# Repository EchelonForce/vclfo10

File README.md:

# Eurorack LFO VCLFO10 

This is a PCB for a eurorack LFO based on the VCLFO10 chip from Electric Druid.

Full writeup here: https://www.robotdialogs.com/2022/09/eurorack-lfo-module-vclfo10.html

This work is licensed under a Creative Commons Attribution-NonCommercial-ShareAlike 4.0 International License. https://creativecommons.org/licenses/by-nc-sa/4.0/

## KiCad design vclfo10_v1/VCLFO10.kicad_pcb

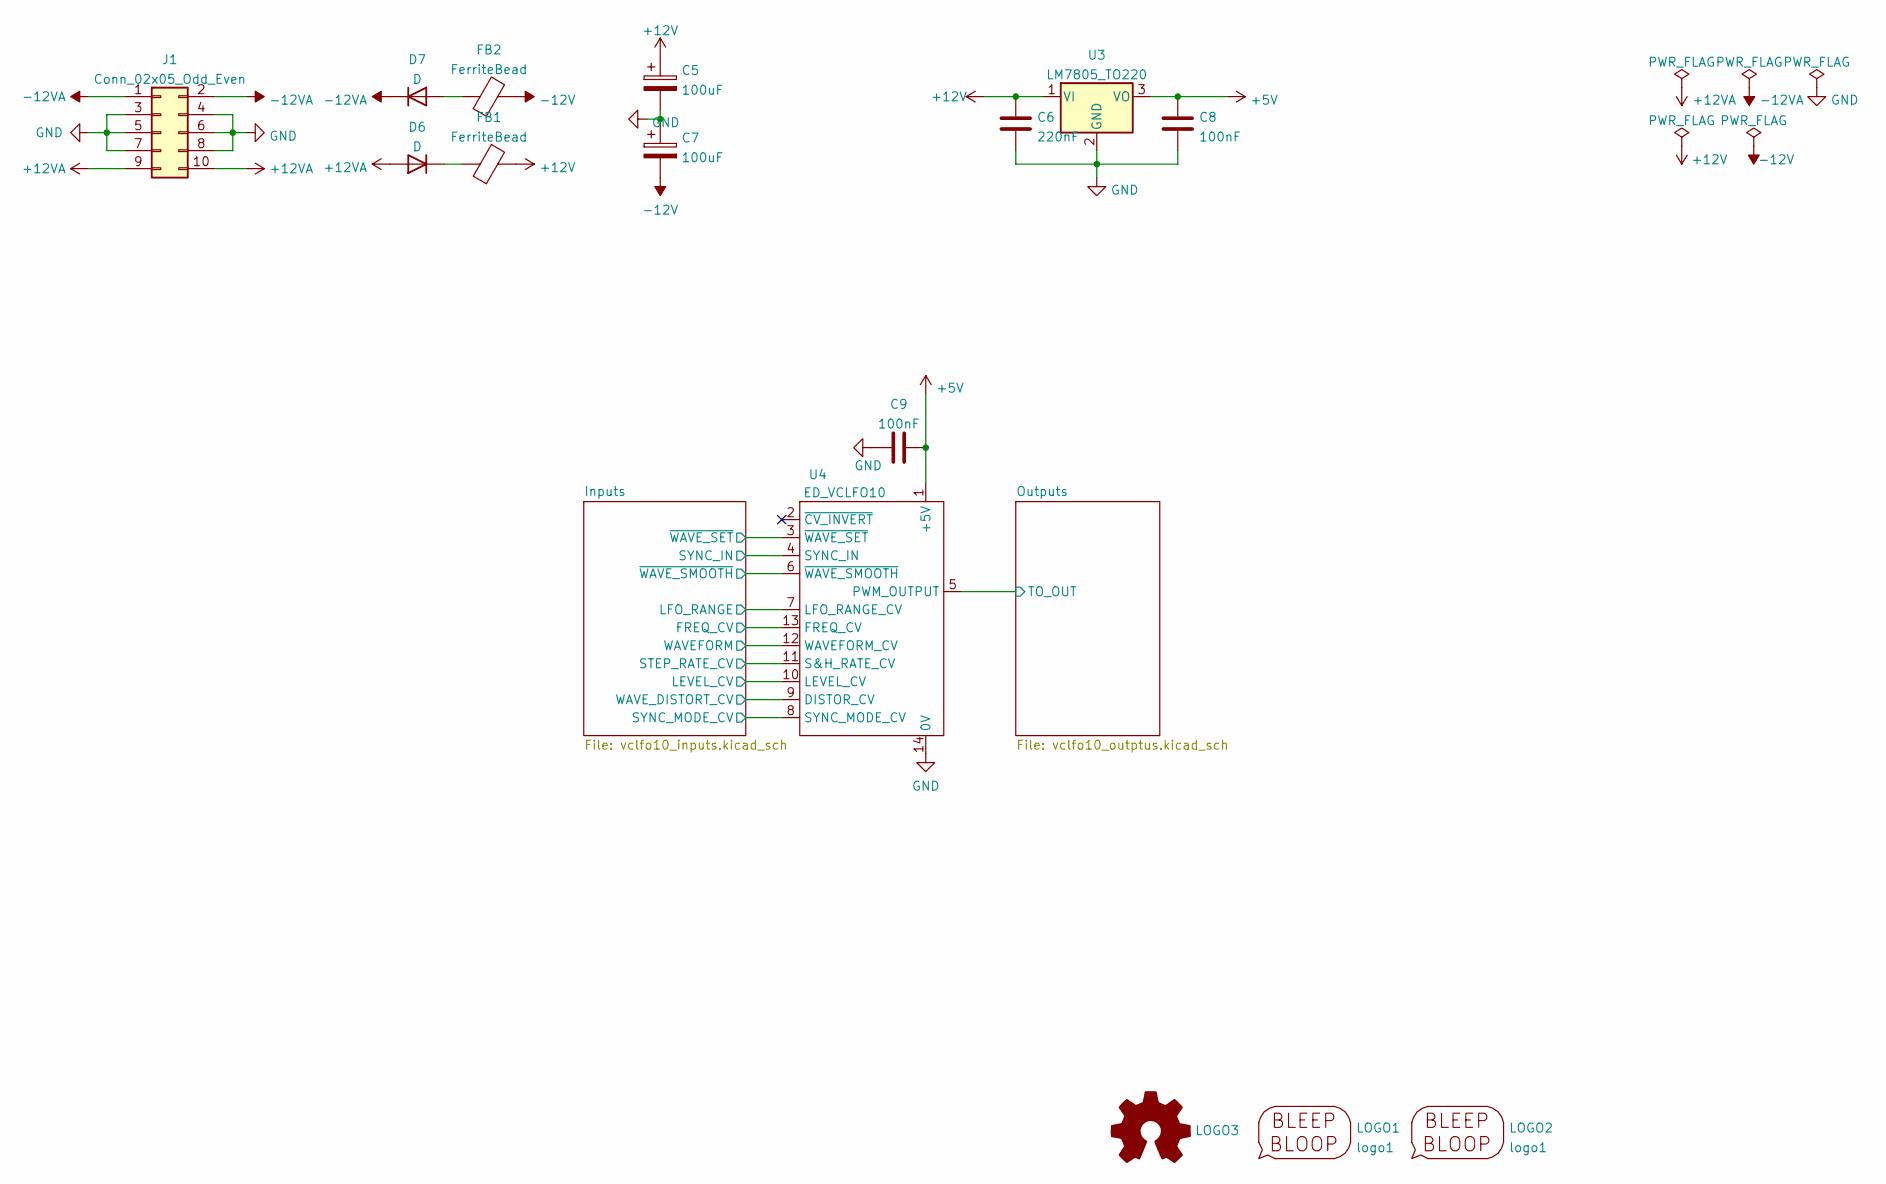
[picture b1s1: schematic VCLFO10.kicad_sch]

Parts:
C5, C7: 100uF; CP_Radial_D5.0mm_P2.50mm
C6: 220nF; C_1206_3216Metric_Pad1.33x1.80mm_HandSolder
C8, C9: 100nF; C_1206_3216Metric_Pad1.33x1.80mm_HandSolder
D6, D7: D; D_A-405_P7.62mm_Horizontal
FB1, FB2: FerriteBead; L_Axial_L6.6mm_D2.7mm_P2.54mm_Vertical_Vishay_IM-2
J1: Conn_02x05_Odd_Even; IDC-Header_2x05_P2.54mm_Vertical
LOGO1: logo1; Logo1
LOGO2: logo1; Logo2
LOGO3: Logo_Open_Hardware_Small; OSHW-Symbol_6.7x6mm_SilkScreen
U3: LM7805_TO220; TO-220-3_Vertical
U4: ED_VCLFO10; DIP-14_W7.62mm_Socket_LongPads

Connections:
+5V: C8.1, C9.2, U3.3 (VO), U4.1 (+5V); also elsewhere on the board
+12V: C5.1, C6.1, FB1.2, U3.1 (VI); also elsewhere on the board
+12VA: D6.2 (A), J1.9, J1.10
-12V: C7.2, FB2.2; also elsewhere on the board
-12VA: D7.1 (K), J1.1, J1.2
/Inputs/FREQ_CV: U4.13 (FREQ_CV); also elsewhere on the board
/Inputs/LEVEL_CV: U4.10 (LEVEL_CV); also elsewhere on the board
/Inputs/LFO_RANGE: U4.7 (LFO_RANGE_CV); also elsewhere on the board
/Inputs/STEP_RATE_CV: U4.11 (S&H_RATE_CV); also elsewhere on the board
/Inputs/SYNC_IN: U4.4 (SYNC_IN); also elsewhere on the board
/Inputs/SYNC_MODE_CV: U4.8 (SYNC_MODE_CV); also elsewhere on the board
/Inputs/WAVEFORM: U4.12 (WAVEFORM_CV); also elsewhere on the board
/Inputs/WAVE_DISTORT_CV: U4.9 (DISTOR_CV); also elsewhere on the board
/Inputs/~WAVE_SET: U4.3 (~WAVE_SET); also elsewhere on the board
/Inputs/~WAVE_SMOOTH: U4.6 (~WAVE_SMOOTH); also elsewhere on the board
/Outputs/TO_OUT: U4.5 (PWM_OUTPUT); also elsewhere on the board
GND: C5.2, C6.2, C7.1, C8.2, C9.1, J1.3, J1.4, J1.5, J1.6, J1.7, J1.8, U3.2 (GND), U4.14 (0V); also elsewhere on the board
unnamed: D6.1 (K), FB1.1
unnamed: D7.2 (A), FB2.1

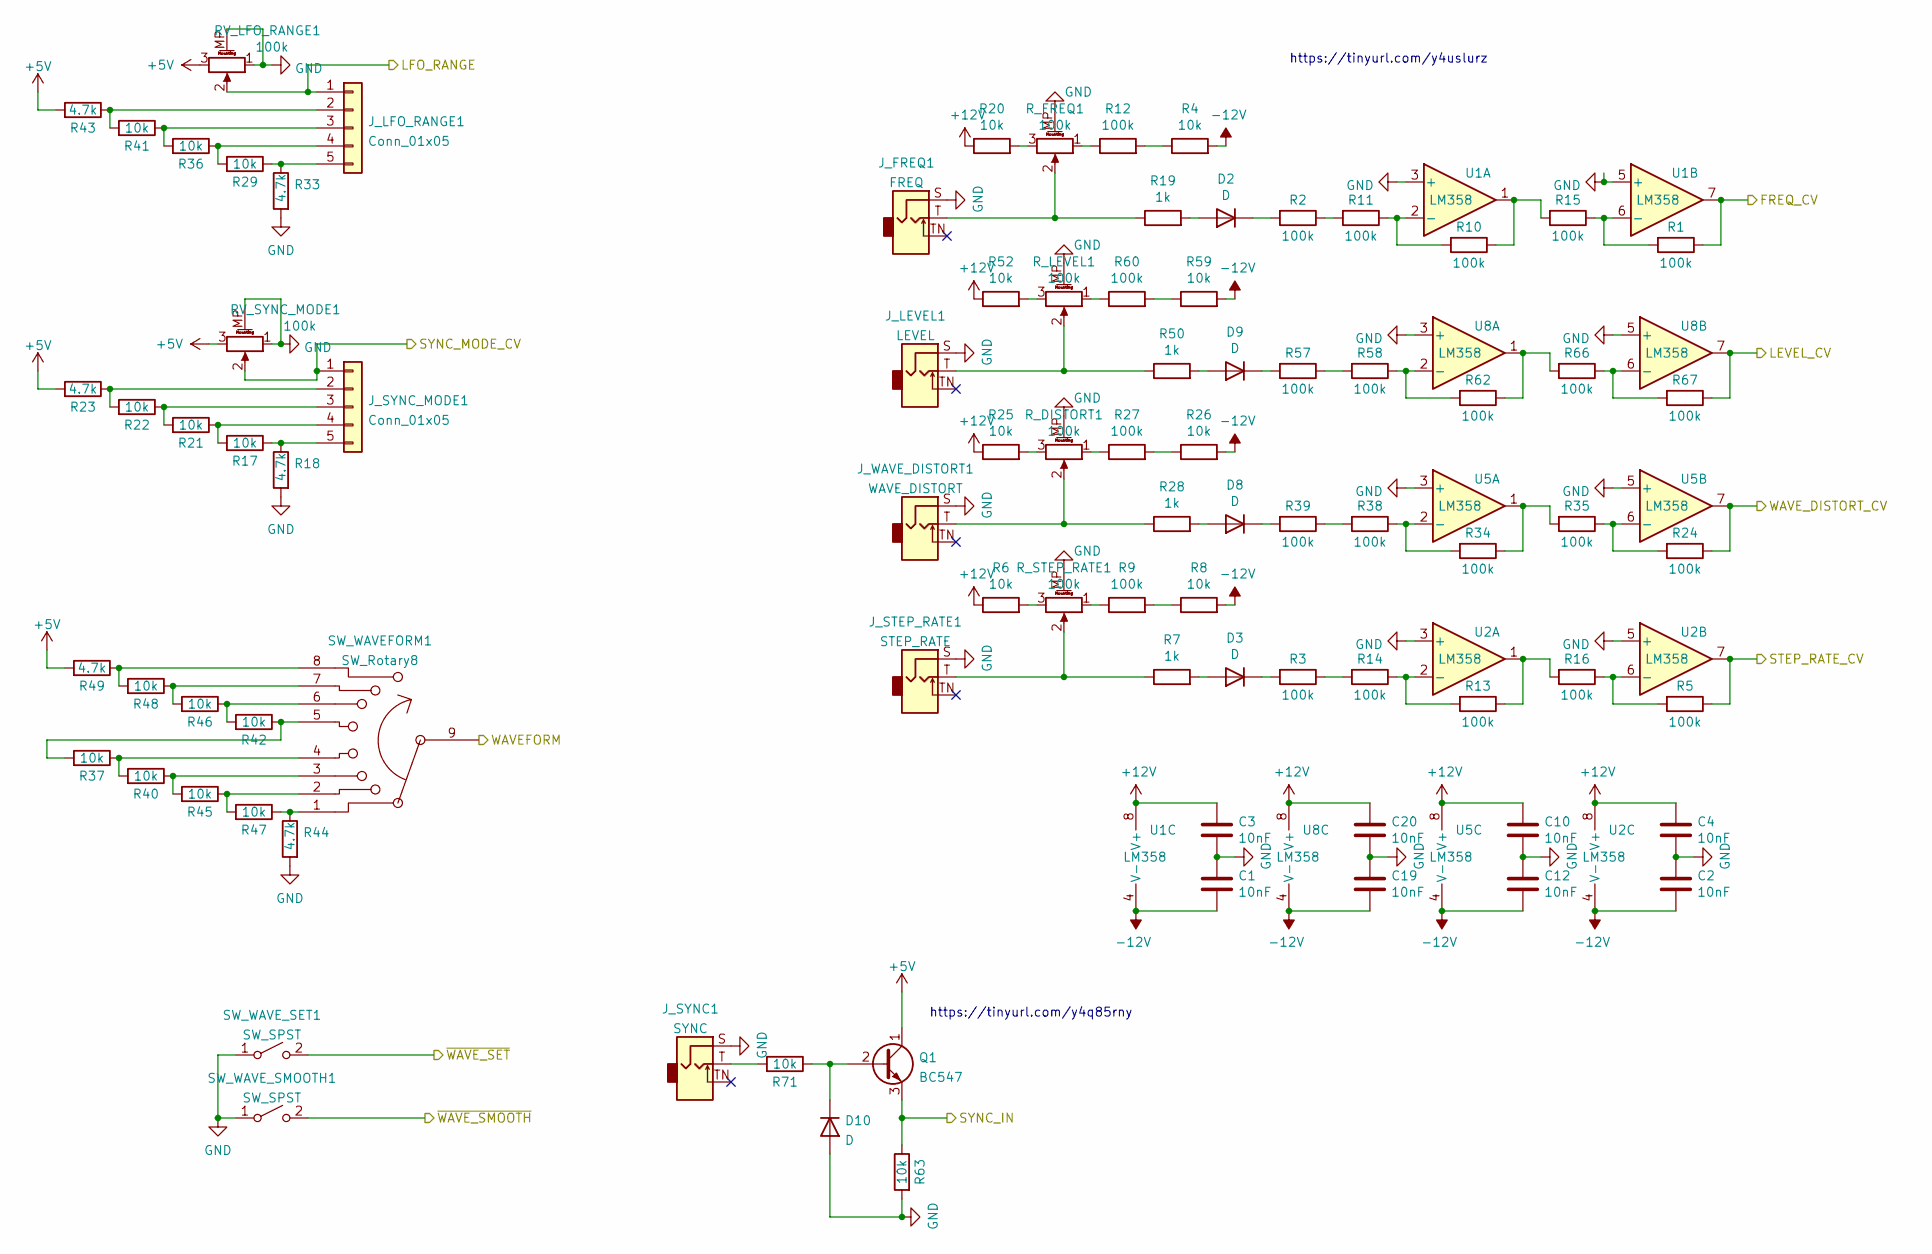
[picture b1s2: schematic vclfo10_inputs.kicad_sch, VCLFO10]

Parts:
C1, C2, C3, C4, C10, C12, C19, C20: 10nF; C_1206_3216Metric_Pad1.33x1.80mm_HandSolder
D2, D3, D8, D9, D10: D; D_A-405_P7.62mm_Horizontal
J_FREQ1: FREQ; Jack_3.5mm_MJ-355W_and_PJ398SM_Vertical
J_LEVEL1: LEVEL; Jack_3.5mm_MJ-355W_and_PJ398SM_Vertical
J_LFO_RANGE1: Conn_01x05; PinSocket_1x05_P2.54mm_Horizontal_no_silkscreen
J_STEP_RATE1: STEP_RATE; Jack_3.5mm_MJ-355W_and_PJ398SM_Vertical
J_SYNC1: SYNC; Jack_3.5mm_MJ-355W_and_PJ398SM_Vertical
J_SYNC_MODE1: Conn_01x05; PinSocket_1x05_P2.54mm_Horizontal_no_silkscreen
J_WAVE_DISTORT1: WAVE_DISTORT; Jack_3.5mm_MJ-355W_and_PJ398SM_Vertical
Q1: BC547; TO-92_Inline_Wide
R1, R2, R3, R5, R9, R10, R11, R12, R13, R14, R15, R16, R24, R27, R34, R35, R38, R39, R57, R58, R60, R62, R66, R67: 100k; R_1206_3216Metric_Pad1.30x1.75mm_HandSolder
R4, R6, R8, R17, R20, R21, R22, R25, R26, R29, R36, R37, R40, R41, R42, R45, R46, R47, R48, R52, R59, R63, R71: 10k; R_1206_3216Metric_Pad1.30x1.75mm_HandSolder
R7, R19, R28, R50: 1k; R_1206_3216Metric_Pad1.30x1.75mm_HandSolder
R18, R23, R33, R43, R44, R49: 4.7k; R_1206_3216Metric_Pad1.30x1.75mm_HandSolder
RV_LFO_RANGE1: 100k; Potentiometer_Alpha_RD901F-40-00D_Single_Vertical_w_3d
RV_SYNC_MODE1: 100k; Potentiometer_Alpha_RD901F-40-00D_Single_Vertical_w_3d
R_DISTORT1: 100k; Potentiometer_Alpha_RD901F-40-00D_Single_Vertical_w_3d
R_FREQ1: 100k; Potentiometer_Alpha_RD901F-40-00D_Single_Vertical_w_3d
R_LEVEL1: 100k; Potentiometer_Alpha_RD901F-40-00D_Single_Vertical_w_3d
R_STEP_RATE1: 100k; Potentiometer_Alpha_RD901F-40-00D_Single_Vertical_w_3d
SW_WAVEFORM1: SW_Rotary8; 8_position_rotary
SW_WAVE_SET1: SW_SPST; SPDT_Toggle
SW_WAVE_SMOOTH1: SW_SPST; SPDT_Toggle
U1, U2, U5, U8: LM358; DIP-8_W7.62mm_Socket_LongPads

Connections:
+5V: Q1.1 (C), R23.2, R43.2, R49.2, RV_LFO_RANGE1.3, RV_SYNC_MODE1.3; also elsewhere on the board
+12V: C3.2, C4.2, C10.2, C20.2, R6.1, R20.1, R25.1, R52.1, U1.8 (V+), U2.8 (V+), U5.8 (V+), U8.8 (V+); also elsewhere on the board
-12V: C1.1, C2.1, C12.1, C19.1, R4.2, R8.2, R26.2, R59.2, U1.4 (V-), U2.4 (V-), U5.4 (V-), U8.4 (V-); also elsewhere on the board
/Inputs/FREQ_CV: R1.1, U1.7; also elsewhere on the board
/Inputs/LEVEL_CV: R67.1, U8.7; also elsewhere on the board
/Inputs/LFO_RANGE: J_LFO_RANGE1.1, RV_LFO_RANGE1.2; also elsewhere on the board
/Inputs/STEP_RATE_CV: R5.1, U2.7; also elsewhere on the board
/Inputs/SYNC_IN: Q1.3 (E), R63.1; also elsewhere on the board
/Inputs/SYNC_MODE_CV: J_SYNC_MODE1.1, RV_SYNC_MODE1.2; also elsewhere on the board
/Inputs/WAVEFORM: SW_WAVEFORM1.9; also elsewhere on the board
/Inputs/WAVE_DISTORT_CV: R24.1, U5.7; also elsewhere on the board
/Inputs/~WAVE_SET: SW_WAVE_SET1.2 (B); also elsewhere on the board
/Inputs/~WAVE_SMOOTH: SW_WAVE_SMOOTH1.2 (B); also elsewhere on the board
GND: C1.2, C2.2, C3.1, C4.1, C10.1, C12.2, C19.2, C20.1, D10.2 (A), J_FREQ1.S, J_LEVEL1.S, J_STEP_RATE1.S, J_SYNC1.S, J_WAVE_DISTORT1.S, R18.2, R33.2, R44.2, R63.2, RV_LFO_RANGE1.1, RV_LFO_RANGE1.MP (MountPin), RV_SYNC_MODE1.1, RV_SYNC_MODE1.MP (MountPin), R_DISTORT1.MP (MountPin), R_FREQ1.MP (MountPin), R_LEVEL1.MP (MountPin), R_STEP_RATE1.MP (MountPin), SW_WAVE_SET1.1 (A), SW_WAVE_SMOOTH1.1 (A), U1.3 (+), U1.5 (+), U2.3 (+), U2.5 (+), U5.3 (+), U5.5 (+), U8.3 (+), U8.5 (+); also elsewhere on the board
unnamed: D2.1 (K), R2.2
unnamed: D2.2 (A), R19.2
unnamed: D3.1 (K), R3.2
unnamed: D3.2 (A), R7.2
unnamed: D8.1 (K), R39.2
unnamed: D8.2 (A), R28.2
unnamed: D9.1 (K), R57.2
unnamed: D9.2 (A), R50.2
unnamed: D10.1 (K), Q1.2 (B), R71.1
unnamed: J_FREQ1.T, R19.1, R_FREQ1.2
unnamed: J_LEVEL1.T, R50.1, R_LEVEL1.2
unnamed: J_LFO_RANGE1.2, R41.2, R43.1
unnamed: J_LFO_RANGE1.3, R36.2, R41.1
unnamed: J_LFO_RANGE1.4, R29.2, R36.1
unnamed: J_LFO_RANGE1.5, R29.1, R33.1
unnamed: J_STEP_RATE1.T, R7.1, R_STEP_RATE1.2
unnamed: J_SYNC1.T, R71.2
unnamed: J_SYNC_MODE1.2, R22.2, R23.1
unnamed: J_SYNC_MODE1.3, R21.2, R22.1
unnamed: J_SYNC_MODE1.4, R17.2, R21.1
unnamed: J_SYNC_MODE1.5, R17.1, R18.1
unnamed: J_WAVE_DISTORT1.T, R28.1, R_DISTORT1.2
unnamed: R6.2, R_STEP_RATE1.3
unnamed: R9.1, R_STEP_RATE1.1
unnamed: R8.1, R9.2
unnamed: R10.1, R15.2, U1.1
unnamed: R10.2, R11.1, U1.2 (-)
unnamed: R2.1, R11.2
unnamed: R12.1, R_FREQ1.1
unnamed: R4.1, R12.2
unnamed: R13.1, R16.2, U2.1
unnamed: R13.2, R14.1, U2.2 (-)
unnamed: R3.1, R14.2
unnamed: R1.2, R15.1, U1.6 (-)
unnamed: R5.2, R16.1, U2.6 (-)
unnamed: R20.2, R_FREQ1.3
unnamed: R25.2, R_DISTORT1.3
unnamed: R27.1, R_DISTORT1.1
unnamed: R26.1, R27.2
unnamed: R34.1, R35.2, U5.1
unnamed: R24.2, R35.1, U5.6 (-)
unnamed: R37.1, R40.2, SW_WAVEFORM1.4
unnamed: R37.2, R42.1, SW_WAVEFORM1.5
unnamed: R34.2, R38.1, U5.2 (-)
unnamed: R38.2, R39.1
unnamed: R40.1, R45.2, SW_WAVEFORM1.3
unnamed: R45.1, R47.2, SW_WAVEFORM1.2
unnamed: R42.2, R46.1, SW_WAVEFORM1.6
unnamed: R44.1, R47.1, SW_WAVEFORM1.1
unnamed: R46.2, R48.1, SW_WAVEFORM1.7
unnamed: R48.2, R49.1, SW_WAVEFORM1.8
unnamed: R52.2, R_LEVEL1.3
unnamed: R58.1, R62.2, U8.2 (-)
unnamed: R57.1, R58.2
unnamed: R60.1, R_LEVEL1.1
unnamed: R59.1, R60.2
unnamed: R62.1, R66.2, U8.1
unnamed: R66.1, R67.2, U8.6 (-)

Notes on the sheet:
https://tinyurl.com/y4uslurz
https://tinyurl.com/y4q85rny

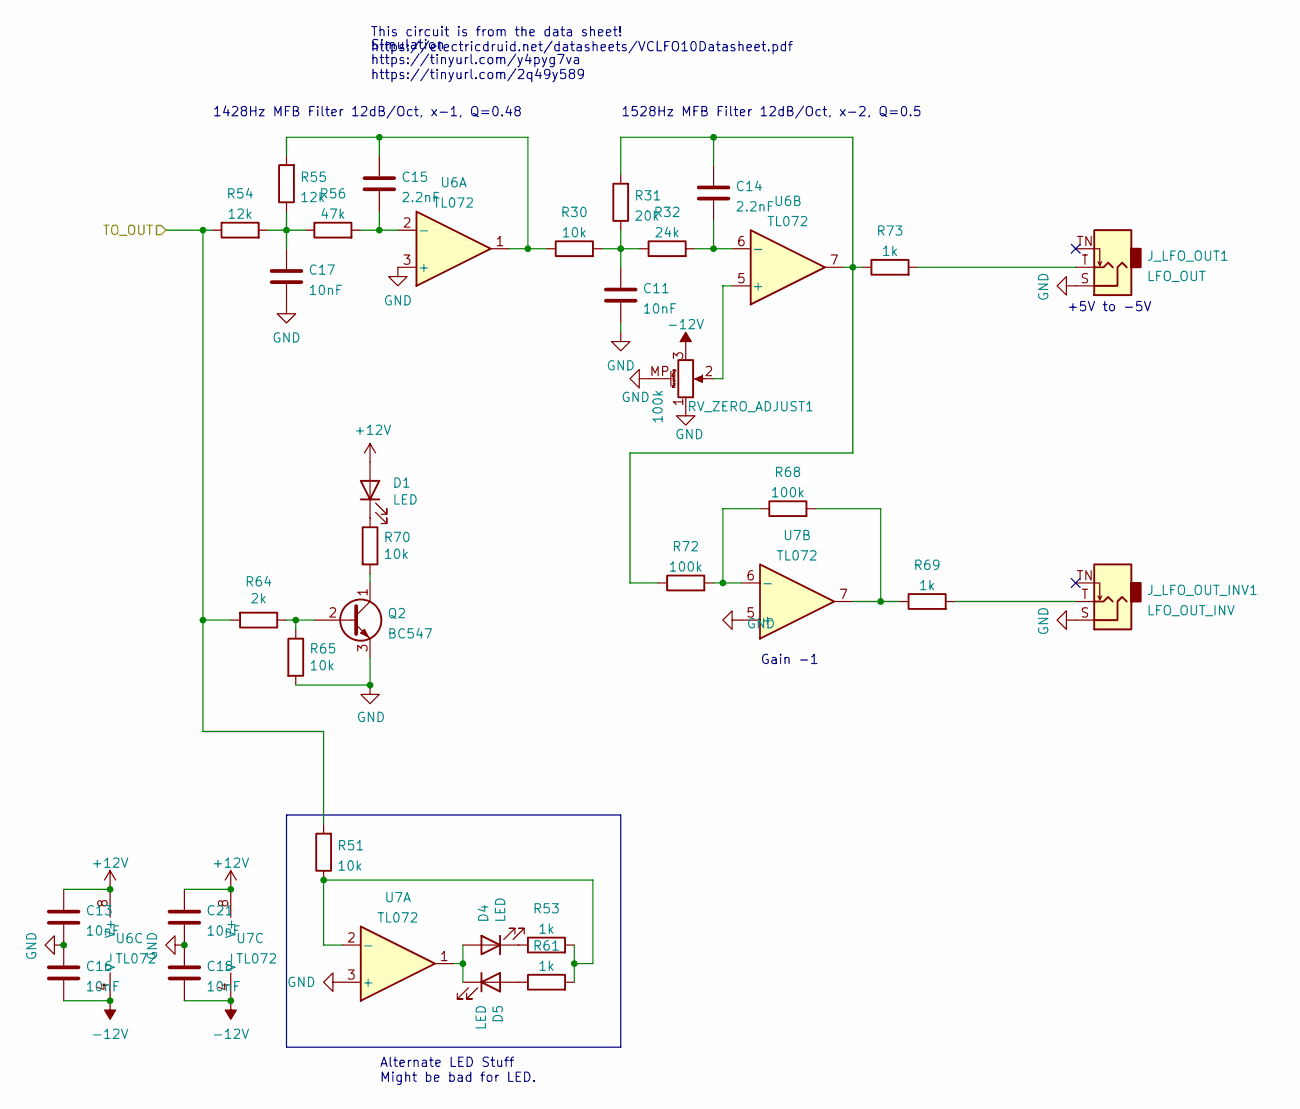
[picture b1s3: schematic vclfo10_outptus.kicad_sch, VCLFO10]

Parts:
C11, C13, C16, C17, C18, C21: 10nF; C_1206_3216Metric_Pad1.33x1.80mm_HandSolder
C14, C15: 2.2nF; C_1206_3216Metric_Pad1.33x1.80mm_HandSolder
D1, D4, D5: LED; PinHeader_1x02_P2.54mm_Vertical
J_LFO_OUT1: LFO_OUT; Jack_3.5mm_MJ-355W_and_PJ398SM_Vertical
J_LFO_OUT_INV1: LFO_OUT_INV; Jack_3.5mm_MJ-355W_and_PJ398SM_Vertical
Q2: BC547; TO-92_Inline_Wide
R30, R51, R65, R70: 10k; R_1206_3216Metric_Pad1.30x1.75mm_HandSolder
R31: 20k; R_1206_3216Metric_Pad1.30x1.75mm_HandSolder
R32: 24k; R_1206_3216Metric_Pad1.30x1.75mm_HandSolder
R53, R61, R69, R73: 1k; R_1206_3216Metric_Pad1.30x1.75mm_HandSolder
R54, R55: 12k; R_1206_3216Metric_Pad1.30x1.75mm_HandSolder
R56: 47k; R_1206_3216Metric_Pad1.30x1.75mm_HandSolder
R64: 2k; R_1206_3216Metric_Pad1.30x1.75mm_HandSolder
R68, R72: 100k; R_1206_3216Metric_Pad1.30x1.75mm_HandSolder
RV_ZERO_ADJUST1: 100k; Potentiometer_Alpha_RD901F-40-00D_Single_Vertical_w_3d
U6, U7: TL072; DIP-8_W7.62mm_Socket_LongPads

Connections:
+12V: C13.1, C21.1, D1.2 (A), U6.8 (V+), U7.8 (V+); also elsewhere on the board
-12V: C16.2, C18.2, RV_ZERO_ADJUST1.3, U6.4 (V-), U7.4 (V-); also elsewhere on the board
/Outputs/TO_OUT: R51.2, R54.1, R64.2; also elsewhere on the board
GND: C11.2, C13.2, C16.1, C17.2, C18.1, C21.2, J_LFO_OUT1.S, J_LFO_OUT_INV1.S, Q2.3 (E), R65.2, RV_ZERO_ADJUST1.1, RV_ZERO_ADJUST1.MP (MountPin), U6.3 (+), U7.3 (+), U7.5 (+); also elsewhere on the board
unnamed: C11.1, R30.2, R31.1, R32.1
unnamed: C14.1, R31.2, R72.1, R73.1, U6.7
unnamed: C14.2, R32.2, U6.6 (-)
unnamed: C15.1, R30.1, R55.2, U6.1
unnamed: C15.2, R56.2, U6.2 (-)
unnamed: C17.1, R54.2, R55.1, R56.1
unnamed: D1.1 (K), R70.1
unnamed: D4.1 (K), R53.1
unnamed: D4.2 (A), D5.1 (K), U7.1
unnamed: D5.2 (A), R61.1
unnamed: J_LFO_OUT1.T, R73.2
unnamed: J_LFO_OUT_INV1.T, R69.2
unnamed: Q2.1 (C), R70.2
unnamed: Q2.2 (B), R64.1, R65.1
unnamed: R51.1, R53.2, R61.2, U7.2 (-)
unnamed: R68.2, R69.1, U7.7
unnamed: R68.1, R72.2, U7.6 (-)
unnamed: RV_ZERO_ADJUST1.2, U6.5 (+)

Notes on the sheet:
1528Hz MFB Filter 12dB/Oct, x-2, Q=0.5
Simulation https://tinyurl.com/y4pyg7va https://tinyurl.com/2q49y589
1428Hz MFB Filter 12dB/Oct, x-1, Q=0.48
+5V to -5V
This circuit is from the data sheet! https://electricdruid.net/datasheets/VCLFO10Datasheet.pdf
Gain -1
Alternate LED Stuff Might be bad for LED.

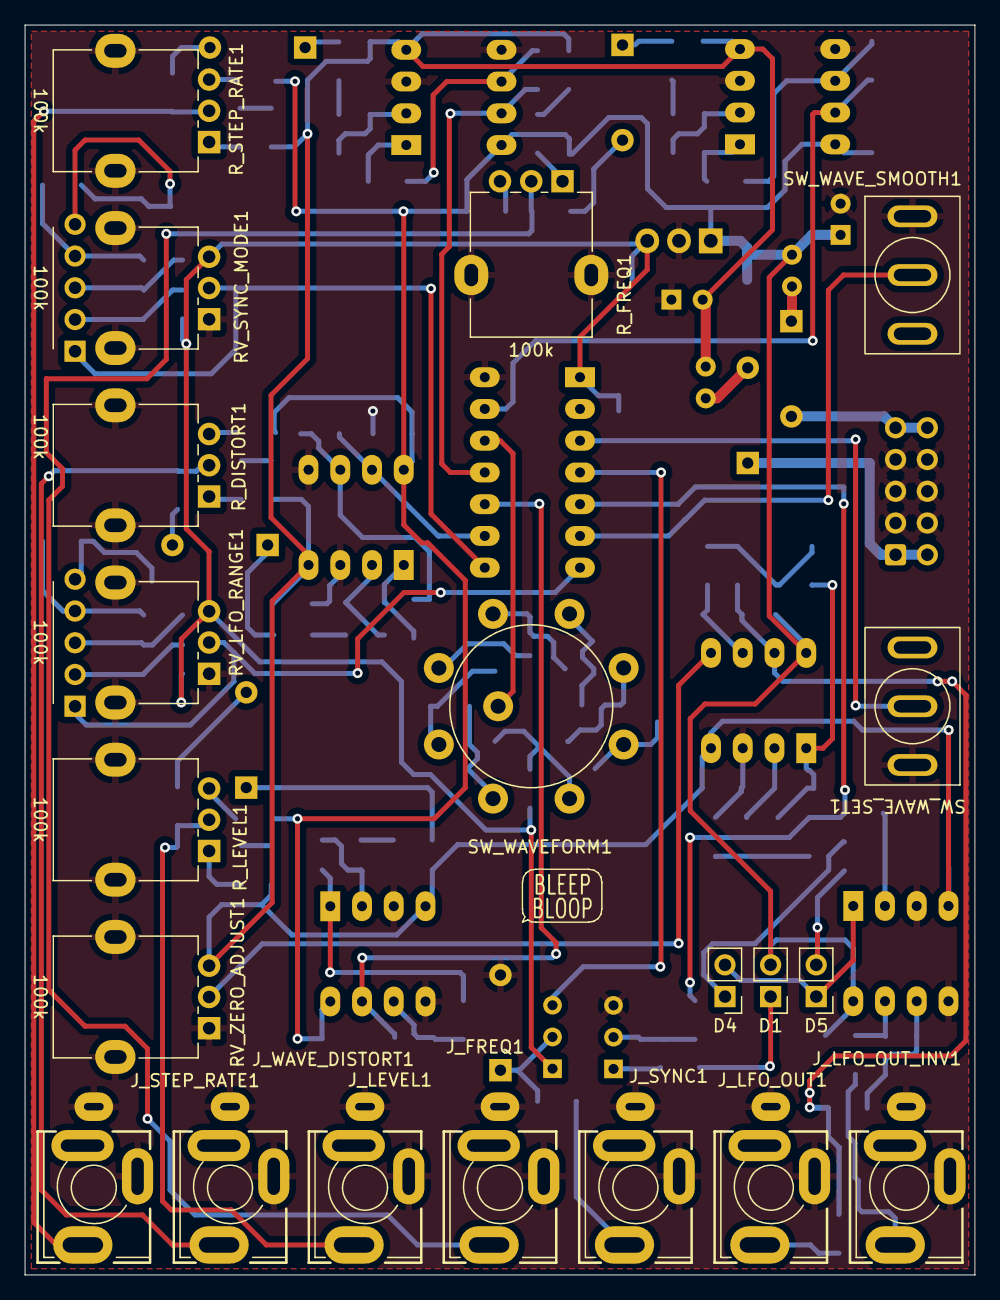
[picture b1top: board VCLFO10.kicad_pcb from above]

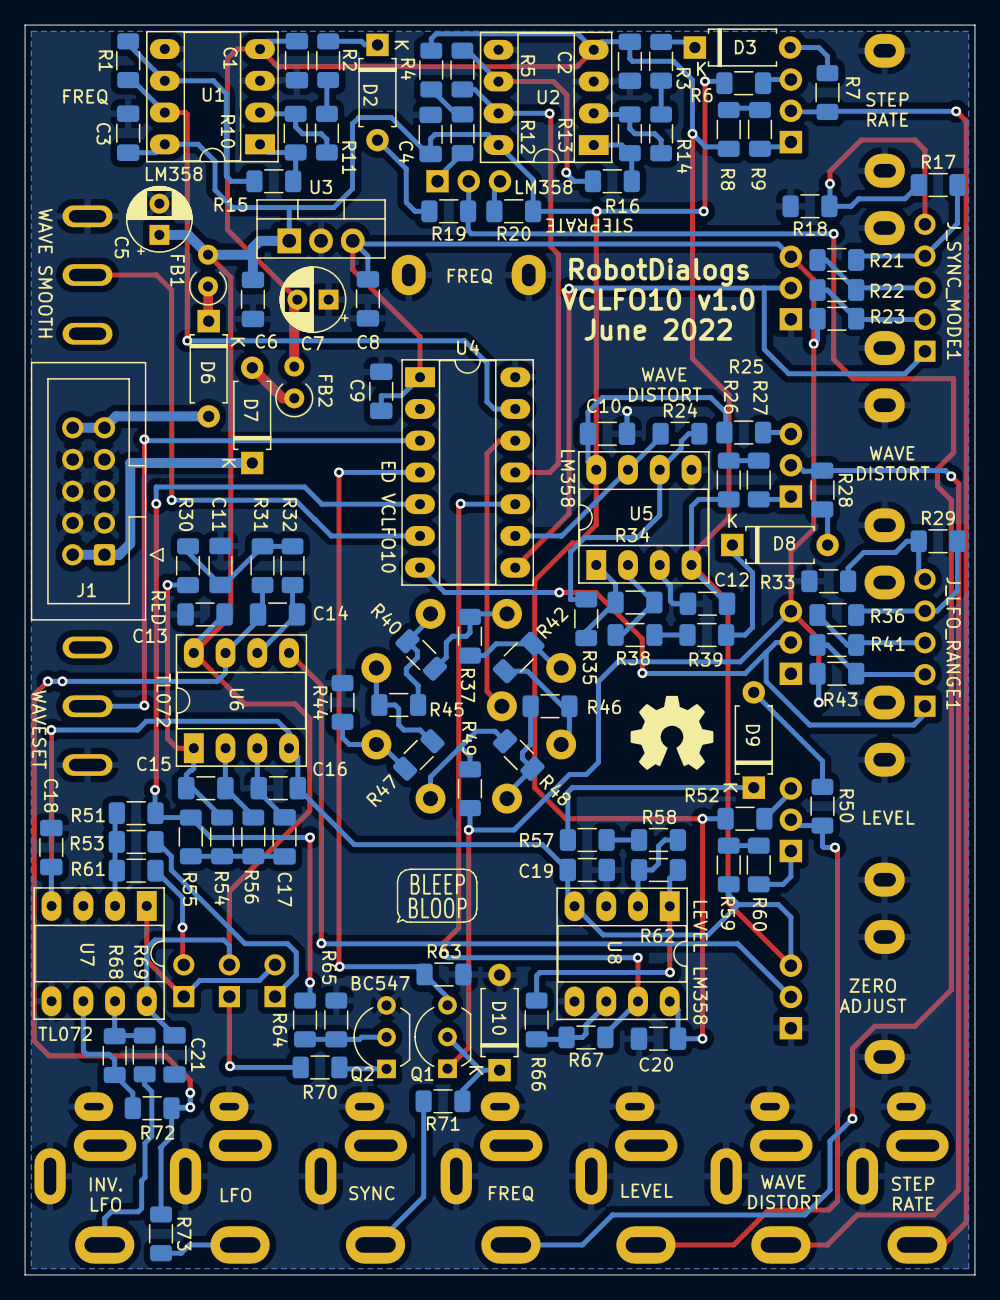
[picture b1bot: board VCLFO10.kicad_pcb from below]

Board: 2 copper layers, 76.0 x 100.0 mm, 139 parts (117 on the bottom side), 95 nets.

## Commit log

2022-06-28 Initial commit with .gitignore
2022-06-28 PCB before routing
2022-06-29 Routing done
2022-06-29 Geographic reannotate and silkscreen cleanup
2022-06-29 Added a help text on silkscreen
2022-06-29 Update title block on schematic and pcb sheets
2022-07-27 Moved pcb files to sub folder
2022-07-27 Add Notes.txt
2022-07-27 Front Panel v1 CAD
2022-07-27 Front Panel v1.1 CAD
2022-09-06 Add readme
2022-09-06 Add schematic pdf
